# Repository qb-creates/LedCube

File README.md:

# LED-Cube

LED Cube Display that projects custom animations using a 5x5x5 matrix of LEDs. The display utilizes an ATmega32 microcontroller utilizes two 16-channel LED drivers.

- Project Video (YouTube): https://www.youtube.com/watch?v=go_lMkQ88TE
- Display Multiplexing: https://en.wikipedia.org/wiki/Multiplexed_display

<div align="center">
  
</div>

<h2> Table of Contents</h2>

1. [Software Used](#software)
2. [Cube Circuit](#cubecircuit)
    - [LED Driver](#leddriver)
    - [Parts List](#cubepartslist) 
3. [Power Consumption](#powerconsumption)
4. [Schematics](#schematics)
    - [Cube Schematic](#cubeschematic)

## 1. Software Used
- Microchip Studio: https://www.microchip.com/en-us/tools-resources/develop/microchip-studio
- AVRDUDE (Flash Uploader): https://github.com/avrdudes/avrdude
- KiCad (PCB Design): https://www.kicad.org
- AutoDesk Fusion 360 Personal (Case Design): https://www.autodesk.com/products/fusion-360/personal

## 2. Display Circuit 
This circuit projects custom animations by utilizing multiplexing and bit-angle modulation for LED dimming. Each layer of the cube consists of 25 LEDs, with their anodes soldered together and their cathodes connected to the CAT4016 constant current sink outputs. The LEDs are arranged into 25 vertical columns, each containing five LEDs stacked across the layers. The cathodes of LEDs within each column are connected together, allowing control of entire columns simultaneously. Five transistors act as switches to control each layer, allowing 5V to be applied to the corresponding anode mesh when the associated transistor is activated. Through multiplexing, all five layers can appear illuminated simultaneously. Communication with the LED drivers is achieved via the SPI protocol.

<div align="center">

</div>

### LED Drivers 
The LED Drivers are chained together. Each driver must receive two bytes of data to control their 16 output channels. Four bytes of data must be sent to the first driver in order to control all 32 output channels. The LEDs are mounted in order (starting from the top left corner of the 32 pin header connector) from 1 to 25. The table below shows which output channel each LED is connected to. 

|_**Cat4016 1 Outputs**_|LED Number|--|_**Cat4016 2 Outputs**_|LED Number|
|:--:|:--:|:--:|:--:|:--:|
|**Byte0**||--|**Byte2**||
|Out0|LED1|--|Out0|LED17|
|Out1|LED2|--|Out1|LED18|
|Out2|LED3|--|Out2|LED19|
|Out3|LED4|--|Out3|LED20|
|Out4|LED5|--|Out4|LED21|
|Out5|LED6|--|Out5|LED22|
|Out6|LED7|--|Out6|LED23|
|Out7|LED8|--|Out7|LED24|
|||--|||
|**Byte1**||--|**Byte3**||
|Out8|LED9|--|Out8|LED25|
|Out9|LED10|--|Out9|N/A|
|Out10|LED11|--|Out10|N/A|
|Out11|LED12|--|Out11|N/A|
|Out12|LED13|--|Out12|N/A|
|Out13|LED14|--|Out13|N/A|
|Out14|LED15|--|Out14|N/A|
|Out15|LED16|--|Out15|N/A|

Because the LED Drivers are daisy chained together, the data must be transmitted in the following order.
* Byte3 (MSB transmitted first) 
* Byte2 (LSB transmitted first) 
* Byte1 (MSB transmitted first) 
* Byte0 (LSB transmitted first) 
---

### Parts List 
|_**Part Number**_|_**Quantity**_|
|:-----|:--------:|
|ATmega32-16PU| x1 |
|10 pin Header connector| x1 |
|32 pin header connector| x1 |
|Header Pins| x5 |
|(Cat4016 discontinued) STP16CPC05MTR LED Driver| x2 |
|10mm Blue Led| x125 |
|16Mhz Crystal| x1 |
|22pF Capacitor 0603 (1608 Metric)| x2 |
|100pF Capacitor 0603 (1608 Metric)| x3 |
|10K Resistor 0603 (1608 Metric)| x1 |
|2.2K Resistor 0603 (1608 Metric)| x2 |
|1K Resistor 0603 (1608 Metric)| x5 |
|1n4148 Diode| x1 |
|BC635 Transistor| x5 |

## 3. Power Consumption <a name="powerconsumption">
|_**Test Condition**_|_**Power Consumption**_|
|:--|:--:|
|Cube circuit with all LEDs powered on. LEDs are supplied with 27mA each.|700mA|

Since each layer of the cube is multiplexed, only 25 LEDs will be illuminated at any given time. As a result, the maximum power consumption for the LEDs is calculated as 27mA multiplied by 25, totaling 681mA. Additionally, the microcontroller itself consumes approximately 20mA. Therefore, the power supply must be capable of providing at least 700mA to ensure stable operation of all components. To allow for adequate headroom, a 1000mA (1A) power supply is recommended.

## 4. Schematics 
### Cube Schematic
<div>
    
</div>

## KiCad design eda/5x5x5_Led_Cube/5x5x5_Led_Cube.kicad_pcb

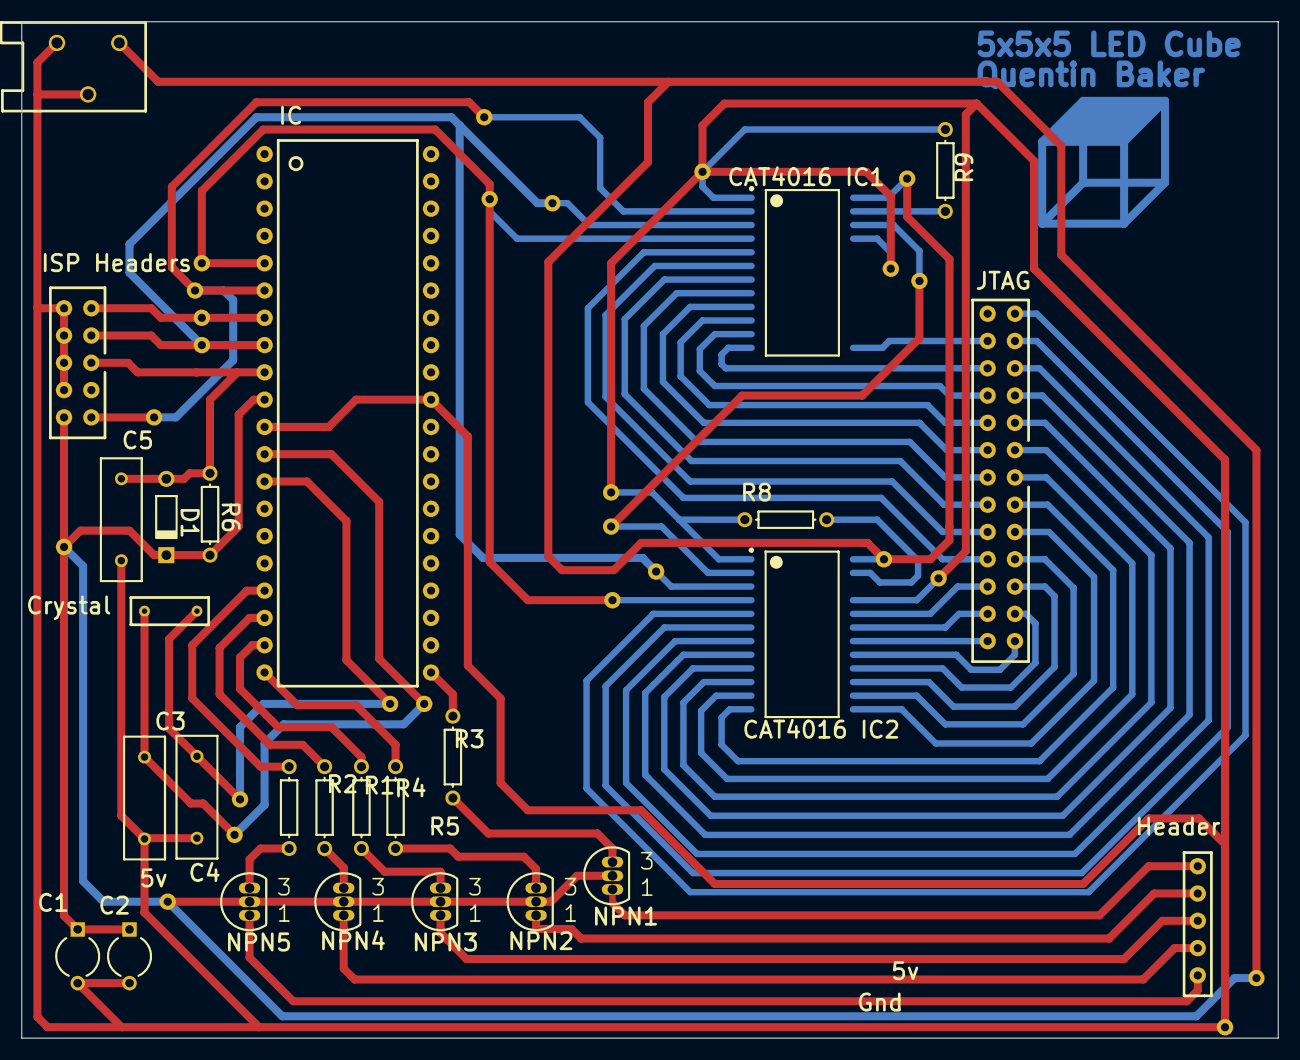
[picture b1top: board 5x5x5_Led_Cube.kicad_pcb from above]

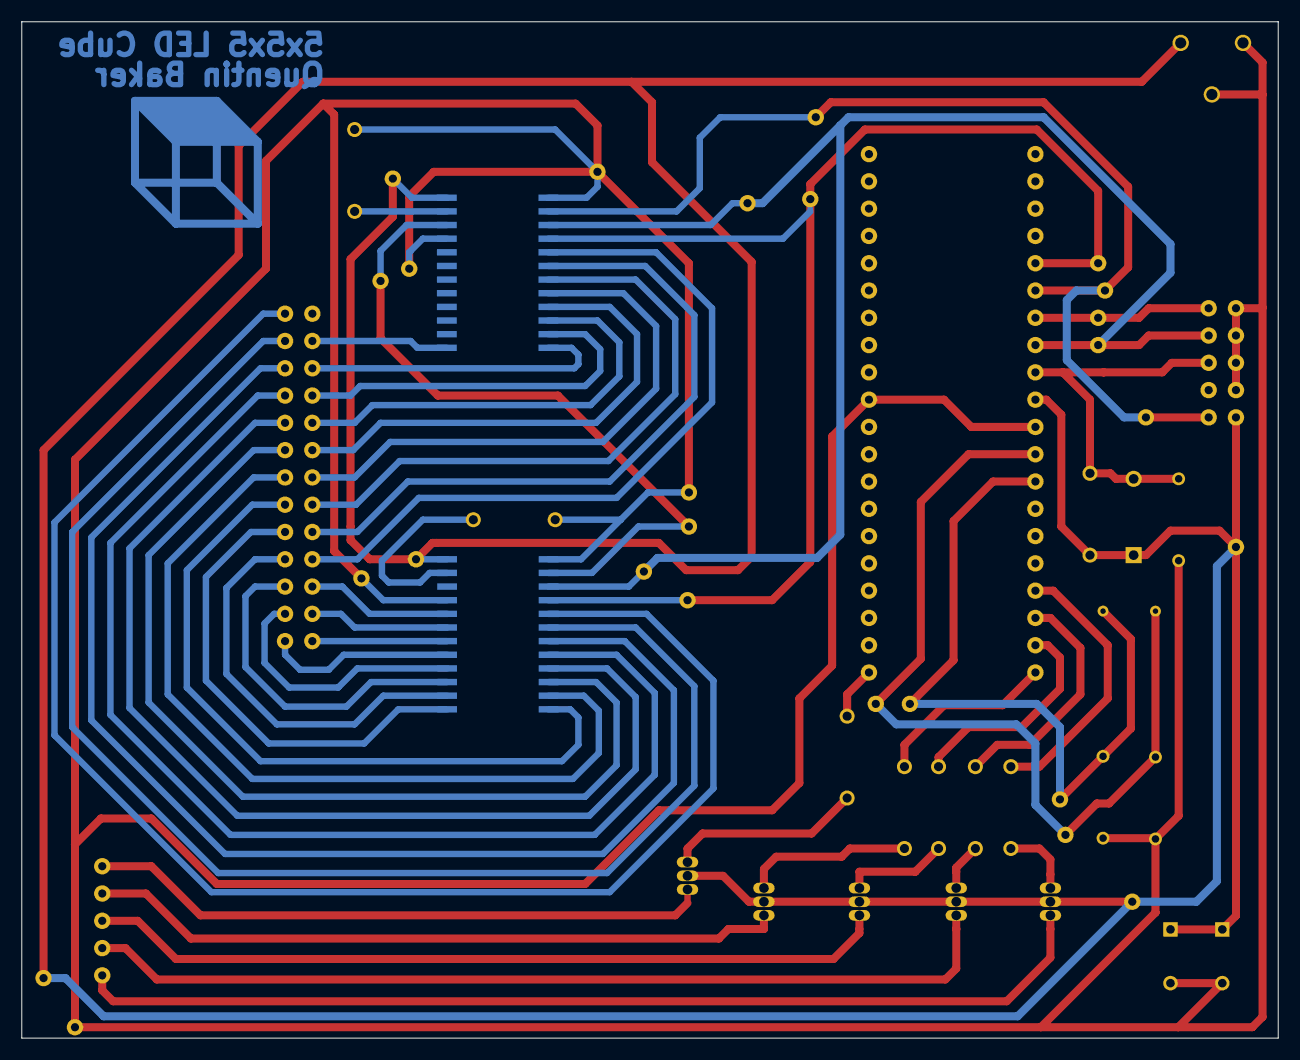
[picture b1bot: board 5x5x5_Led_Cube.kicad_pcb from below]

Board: 2 copper layers, 117.0 x 94.6 mm, 27 parts (27 on the bottom side), 11 nets.

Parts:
C1, C2: Cap2; CAPR5-4X5
C3, C4, C5: Cap; RAD-0.3
CAT4016 IC1, CAT4016 IC2: CAT4016; Cat4016
Crystal: Crystal
D1: Diode 1N914; DO-35
Header: Header Component; Layer_Headers
IC: Component_1; Atmega32DIP
ISP Headers: ISP; Shrouder Header
JTAG: Component_1; Shrouder Header 13
NPN1, NPN2, NPN3, NPN4, NPN5: BC635; BCY-W3
Power: Power_component; Barrel Jack
R1, R2, R3, R4, R5, R6, R8: Res1; AXIAL-0.3
R9: 2.2K; AXIAL-0.3

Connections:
5V: IC.10, ISP Headers.2, Power.1
/5V: C2.1, CAT4016 IC1.24 (VDD), CAT4016 IC2.24 (VDD), D1.2 (K), NPN1.2 (C), NPN2.2 (C), NPN3.2 (C), NPN4.2 (C), NPN5.2 (C), R6.1
/Gnd: C2.2, C3.1, C4.1, C5.1, CAT4016 IC1.1 (GND), CAT4016 IC1.21 (BNK), CAT4016 IC2.1 (GND), CAT4016 IC2.21 (BNK), R8.1, R9.1
GND: IC.11, IC.31, ISP Headers.4, ISP Headers.6, ISP Headers.8, ISP Headers.10, Power.2, Power.3
unnamed: D1.1 (A), R6.2
NetC3_2: Crystal.1, IC.12
NetC4_2: Crystal.2, IC.13
NetC5_2: IC.9, ISP Headers.5
NetCAT4016 IC1_2: IC.6, ISP Headers.1
NetCAT4016 IC1_3: IC.8, ISP Headers.7
NetIC_7: IC.7, ISP Headers.9

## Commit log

2021-11-09 Added images
2021-11-09 README.md edited online with Bitbucket
2021-11-09 Adding solution
2022-02-14 Changing to Github
2022-02-14 Fixed image path in ReadMe file
2025-02-24 Update README.md
    Updated Software Used section of readme
2025-02-24 Add files via upload
    Adding new led cube image
2025-02-24 Update README.md
    Updated the read me to include the new led cub image. Updated the LED Drivers section.
2025-02-24 Update README.md
    Added schematic and power consumption sections
2025-02-24 - Updated git ignore to include kicad projects
2025-02-24 - removed old schematic pdf and added new led cube schematic - Added led cube kicad solution - Added new schematic to the readme
2025-02-24 - Updated power consumption section of the read me.
2025-02-24 - Updated the Display Circuit description
2025-02-24 - Removed links from the parts list
2025-02-24 - Removed clock and replaced it with cube
2025-03-01 Update README.md
    Updated led cube image on readme
